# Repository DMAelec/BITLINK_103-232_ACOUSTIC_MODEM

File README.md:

# BITLINK 103-232 ACOUSTIC MODEM

A 74HC943 based acoustic modem running at 300 baud for retro computers.

WORK IN PROGRESS

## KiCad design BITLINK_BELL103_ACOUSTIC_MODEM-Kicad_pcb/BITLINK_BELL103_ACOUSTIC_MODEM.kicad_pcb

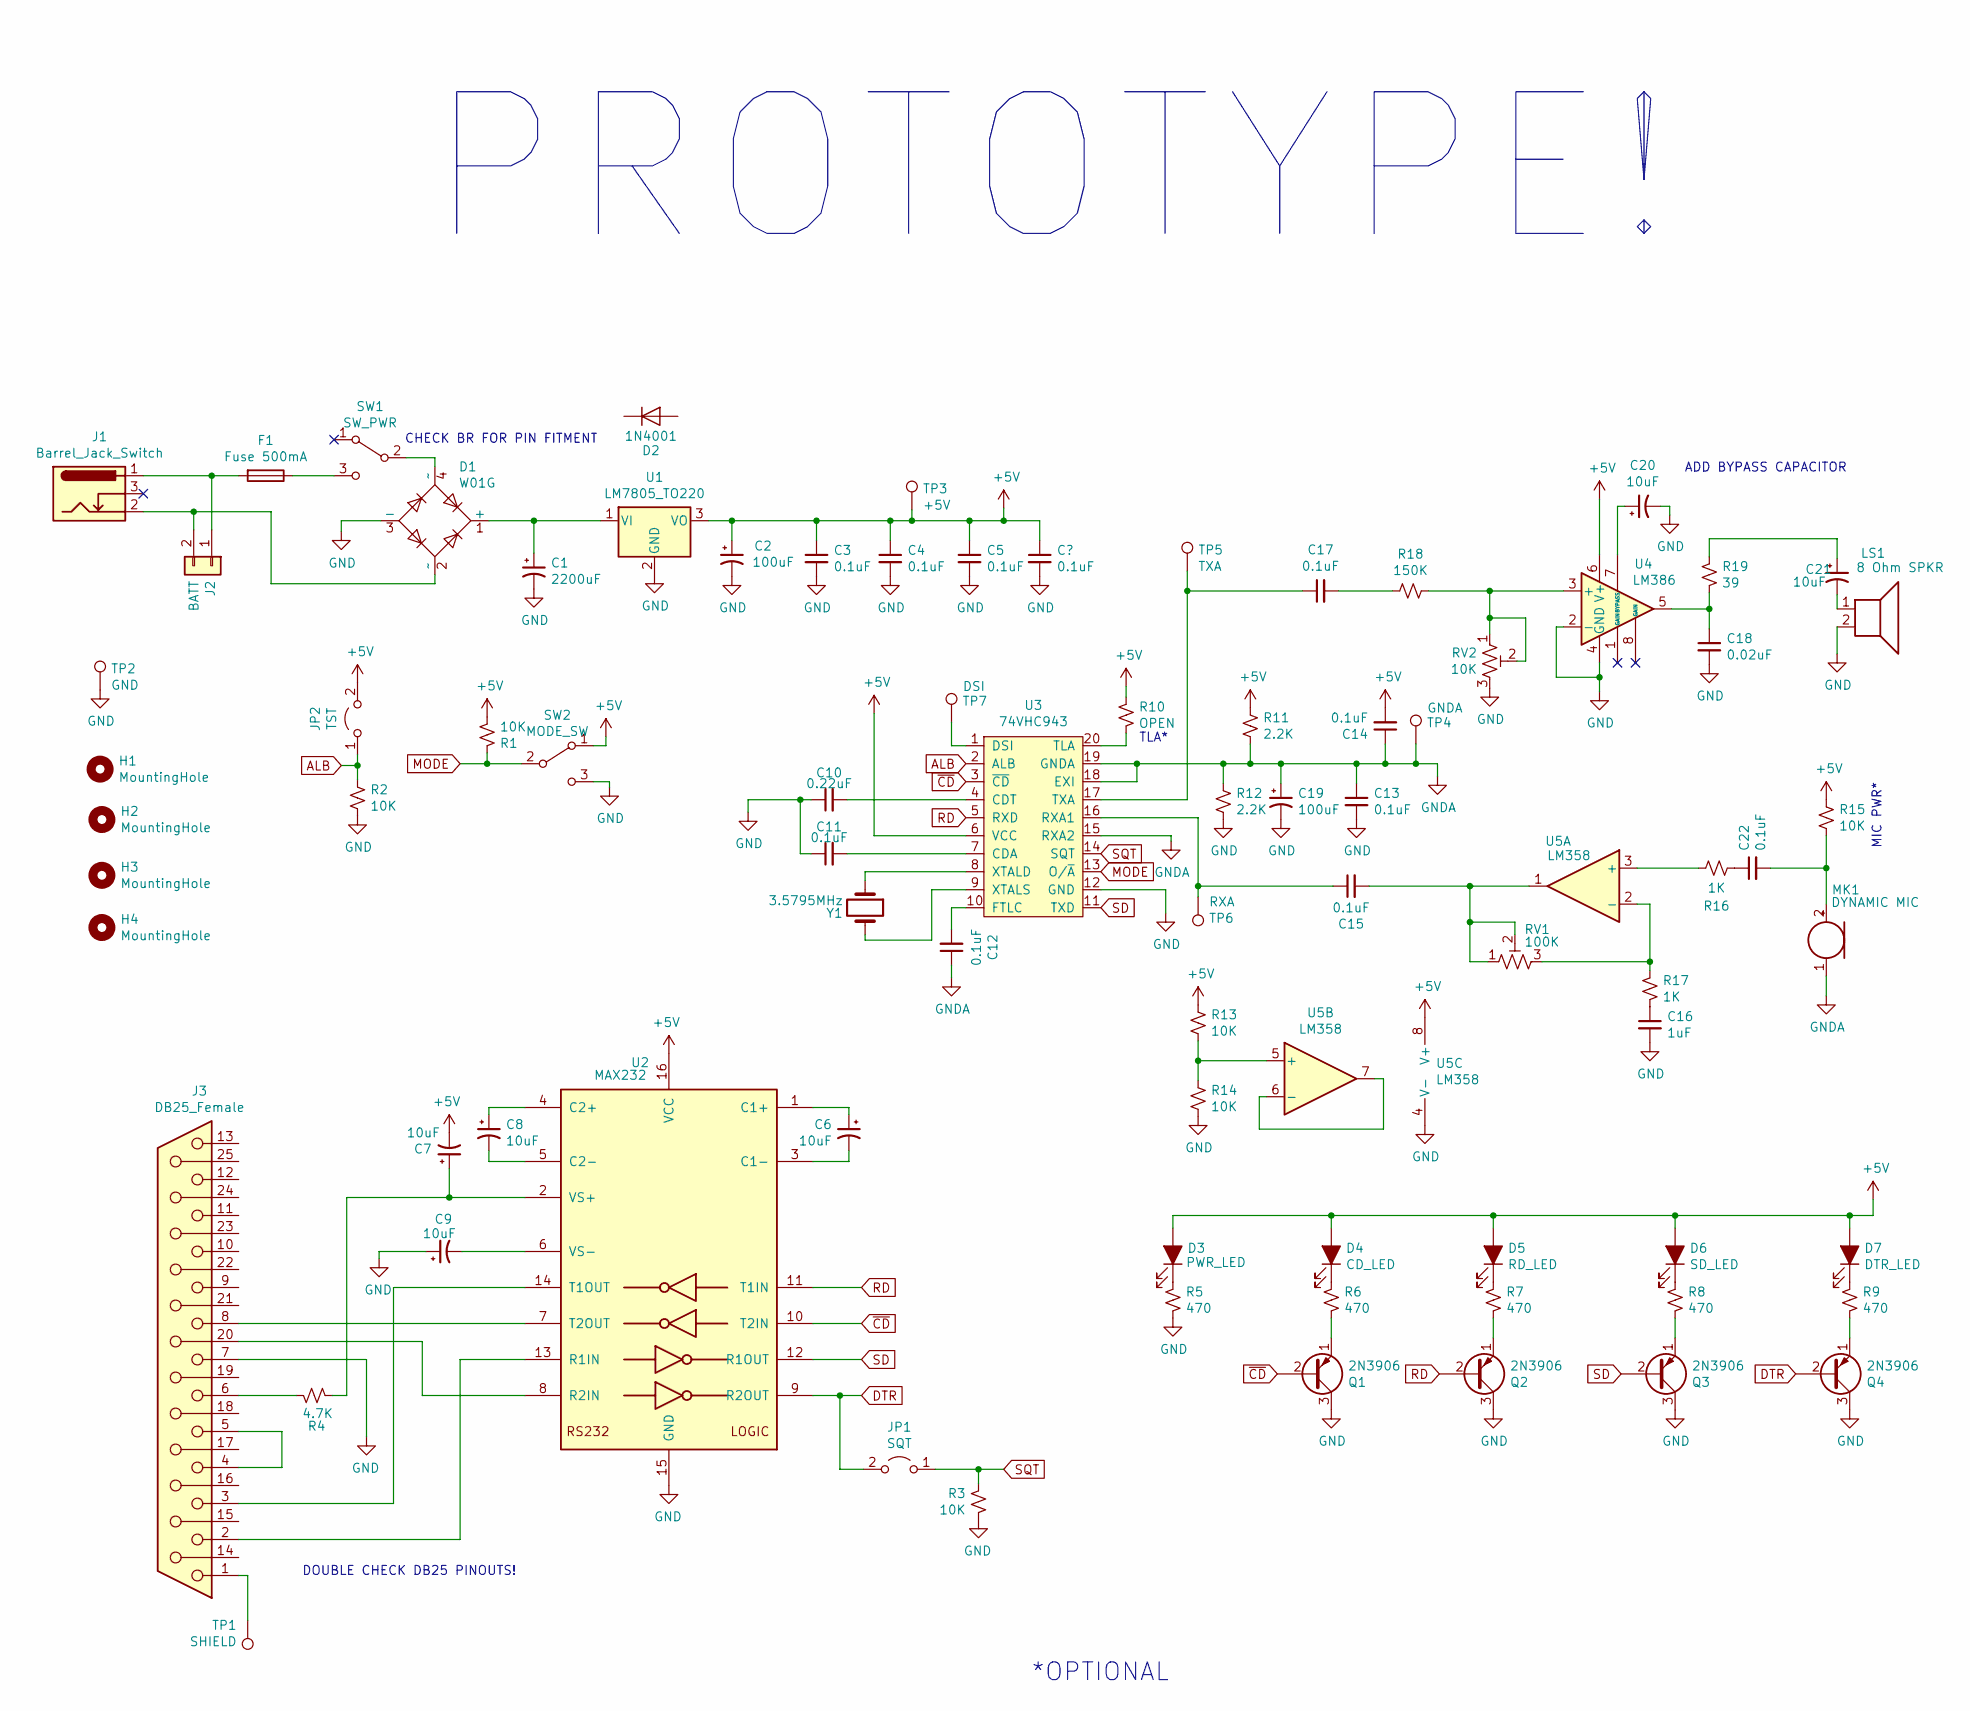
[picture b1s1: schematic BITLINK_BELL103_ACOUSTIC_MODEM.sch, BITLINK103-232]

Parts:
C1: 2200uF; CP_Axial_L30.0mm_D18.0mm_P35.00mm_Horizontal
C2, C19: 100uF; CP_Radial_D8.0mm_P3.80mm
C3, C4, C5, C11, C12, C13, C14, C15, C17, C22: 0.1uF; C_Disc_D5.1mm_W3.2mm_P5.00mm
C6, C7, C8, C9, C20, C21: 10uF; CP_Radial_D5.0mm_P2.50mm
C10: 0.22uF; C_Disc_D5.1mm_W3.2mm_P5.00mm
C16: 1uF; C_Disc_D5.1mm_W3.2mm_P5.00mm
C18: 0.02uF; C_Disc_D5.1mm_W3.2mm_P5.00mm
D1: W01G; Diode_Bridge_Round_D9.8mm
D2: 1N4001; D_DO-41_SOD81_P10.16mm_Horizontal
D3: PWR_LED; LED_D5.0mm
D4: CD_LED; LED_D5.0mm
D5: RD_LED; LED_D5.0mm
D6: SD_LED; LED_D5.0mm
D7: DTR_LED; LED_D5.0mm
F1: Fuse 500mA; Fuseholder_Cylinder-5x20mm_Schurter_0031_8201_Horizontal_Op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
H1, H2, H3, H4: MountingHole; MountingHole_3.2mm_M3
J1: Barrel_Jack_Switch; BarrelJack_Horizontal
J2: BATT; TerminalBlock_bornier-2_P5.08mm
J3: DB25_Female; DSUB-25_Female_Horizontal_P2.77x2.84mm_EdgePinOffset4.94mm_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
JP1: SQT; PinHeader_1x02_P2.54mm_Vertical
JP2: TST; PinHeader_1x02_P2.54mm_Vertical
LS1: 8 Ohm SPKR; Molex_KK-254_AE-6410-02A_1x02_P2.54mm_Vertical
MK1: DYNAMIC MIC; Molex_KK-254_AE-6410-02A_1x02_P2.54mm_Vertical
Q1, Q2, Q3, Q4: 2N3906; TO-92_Wide
R1, R2, R3, R13, R14, R15: 10K; R_Axial_DIN0207_L6.3mm_D2.5mm_P10.16mm_Horizontal
R4: 4.7K; R_Axial_DIN0207_L6.3mm_D2.5mm_P10.16mm_Horizontal
R5, R6, R7, R8, R9: 470; R_Axial_DIN0207_L6.3mm_D2.5mm_P10.16mm_Horizontal
R10: OPEN; R_Axial_DIN0207_L6.3mm_D2.5mm_P10.16mm_Horizontal
R11, R12: 2.2K; R_Axial_DIN0207_L6.3mm_D2.5mm_P10.16mm_Horizontal
R16, R17: 1K; R_Axial_DIN0207_L6.3mm_D2.5mm_P10.16mm_Horizontal
R18: 150K; R_Axial_DIN0207_L6.3mm_D2.5mm_P10.16mm_Horizontal
R19: 39; R_Axial_DIN0207_L6.3mm_D2.5mm_P10.16mm_Horizontal
RV1: 100K; Potentiometer_Piher_PT-10-V10_Vertical
RV2: 10K; Potentiometer_Piher_PT-10-V10_Vertical
SW1: SW_PWR; SW_CK_E101J1ABE2_SPDT_RIGHT_ANGLE_ROCKER
SW2: MODE_SW; SW_CK_E101J1ABE2_SPDT_RIGHT_ANGLE_ROCKER
TP1: SHIELD; TestPoint_THTPad_D2.5mm_Drill1.2mm
TP2: GND; TestPoint_THTPad_D2.5mm_Drill1.2mm
TP3: +5V; TestPoint_THTPad_D2.5mm_Drill1.2mm
TP4: GNDA; TestPoint_THTPad_D2.5mm_Drill1.2mm
TP5: TXA; TestPoint_THTPad_D2.5mm_Drill1.2mm
TP6: RXA; TestPoint_THTPad_D2.5mm_Drill1.2mm
TP7: DSI; TestPoint_THTPad_D2.5mm_Drill1.2mm
U1: LM7805_TO220; TO-220-3_Horizontal_TabDown
U2: MAX232; DIP-16_W7.62mm_LongPads
U3: 74VHC943; DIP-20_W7.62mm_LongPads
U4: LM386; DIP-8_W7.62mm_LongPads
U5: LM358; DIP-8_W7.62mm_LongPads
Y1: 3.5795MHz; Crystal_HC49-U_Vertical

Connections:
+5V: C2.1, C3.1, C4.1, C5.1, C7.2, C14.2, D3.2 (A), D4.2 (A), D5.2 (A), D6.2 (A), D7.2 (A), JP2.2 (B), R1.2, R10.1, R11.1, R13.1, R15.1, SW2.1 (A), TP3.1, U1.3 (VO), U2.16 (VCC), U3.6 (VCC), U4.6 (V+), U5.8 (V+)
ALB: JP2.1 (A), R2.1, U3.2 (ALB)
DTR: JP1.2 (B), Q4.2 (B), U2.9 (R2OUT)
GND: C1.2, C2.2, C3.2, C4.2, C5.2, C9.1, C10.1, C11.1, C13.2, C16.2, C18.2, C19.2, C20.2, D1.3 (-), J3.7, LS1.2, Q1.3 (C), Q2.3 (C), Q3.3 (C), Q4.3 (C), R2.2, R3.2, R5.2, R12.2, R14.2, RV2.3, SW2.3 (C), TP2.1, U1.2 (GND), U2.15 (GND), U3.12 (GND), U4.2 (-), U4.4 (GND), U5.4 (V-)
GNDA: C12.1, C13.1, C14.1, C19.1, MK1.1 (-), R11.2, R12.1, TP4.1, U3.15 (RXA2), U3.18 (EXI), U3.19 (GNDA)
MODE: R1.1, SW2.2 (B), U3.13 (O/~A)
unnamed: C1.1, D1.1 (+), U1.1 (VI)
unnamed: C6.1, U2.1 (C1+)
unnamed: C6.2, U2.3 (C1-)
unnamed: C7.1, R4.1, U2.2 (VS+)
unnamed: C8.1, U2.4 (C2+)
unnamed: C8.2, U2.5 (C2-)
unnamed: C9.2, U2.6 (VS-)
unnamed: C10.2, U3.4 (CDT)
unnamed: C11.2, U3.7 (CDA)
unnamed: C12.2, U3.10 (FTLC)
unnamed: C15.1, TP6.1, U3.16 (RXA1)
unnamed: C15.2, RV1.1, RV1.2, U5.1
unnamed: C16.1, R17.2
unnamed: C17.1, TP5.1, U3.17 (TXA)
unnamed: C17.2, R18.2
unnamed: C18.1, R19.2, U4.5
unnamed: C20.1, U4.7 (BYPASS)
unnamed: C21.1, R19.1
unnamed: C21.2, LS1.1
unnamed: C22.1, R16.1
unnamed: C22.2, MK1.2 (+), R15.2
unnamed: D1.2 (~~), J1.2, J2.2
unnamed: D1.4 (~~), SW1.2 (B)
unnamed: D3.1 (K), R5.1
unnamed: D4.1 (K), R6.1
unnamed: D5.1 (K), R7.1
unnamed: D6.1 (K), R8.1
unnamed: D7.1 (K), R9.1
unnamed: F1.1, SW1.3 (C)
unnamed: F1.2, J1.1, J2.1
unnamed: J3.1, TP1.1
unnamed: J3.2, U2.13 (R1IN)
unnamed: J3.3, U2.14 (T1OUT)
unnamed: J3.4, J3.5
unnamed: J3.6, R4.2
unnamed: J3.8, U2.7 (T2OUT)
unnamed: J3.20, U2.8 (R2IN)
unnamed: Q1.1 (E), R6.2
unnamed: Q2.1 (E), R7.2
unnamed: Q3.1 (E), R8.2
unnamed: Q4.1 (E), R9.2
unnamed: R10.2, U3.20 (TLA)
unnamed: R13.2, R14.1, U5.5 (+)
unnamed: R16.2, U5.3 (+)
unnamed: R17.1, RV1.3, U5.2 (-)
unnamed: R18.1, RV2.1, RV2.2, U4.3 (+)
unnamed: TP7.1, U3.1 (DSI)
unnamed: U3.8 (XTALD), Y1.1
unnamed: U3.9 (XTALS), Y1.2
unnamed: U5.6 (-), U5.7
RD: Q2.2 (B), U2.11 (T1IN), U3.5 (RXD)
SD: Q3.2 (B), U2.12 (R1OUT), U3.11 (TXD)
SQT: JP1.1 (A), R3.1, U3.14 (SQT)
~CD: Q1.2 (B), U2.10 (T2IN), U3.3 (~CD)

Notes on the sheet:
MIC PWR*
PROTOTYPE!
*OPTIONAL
TLA*
DOUBLE CHECK DB25 PINOUTS!
ADD BYPASS CAPACITOR
CHECK BR FOR PIN FITMENT

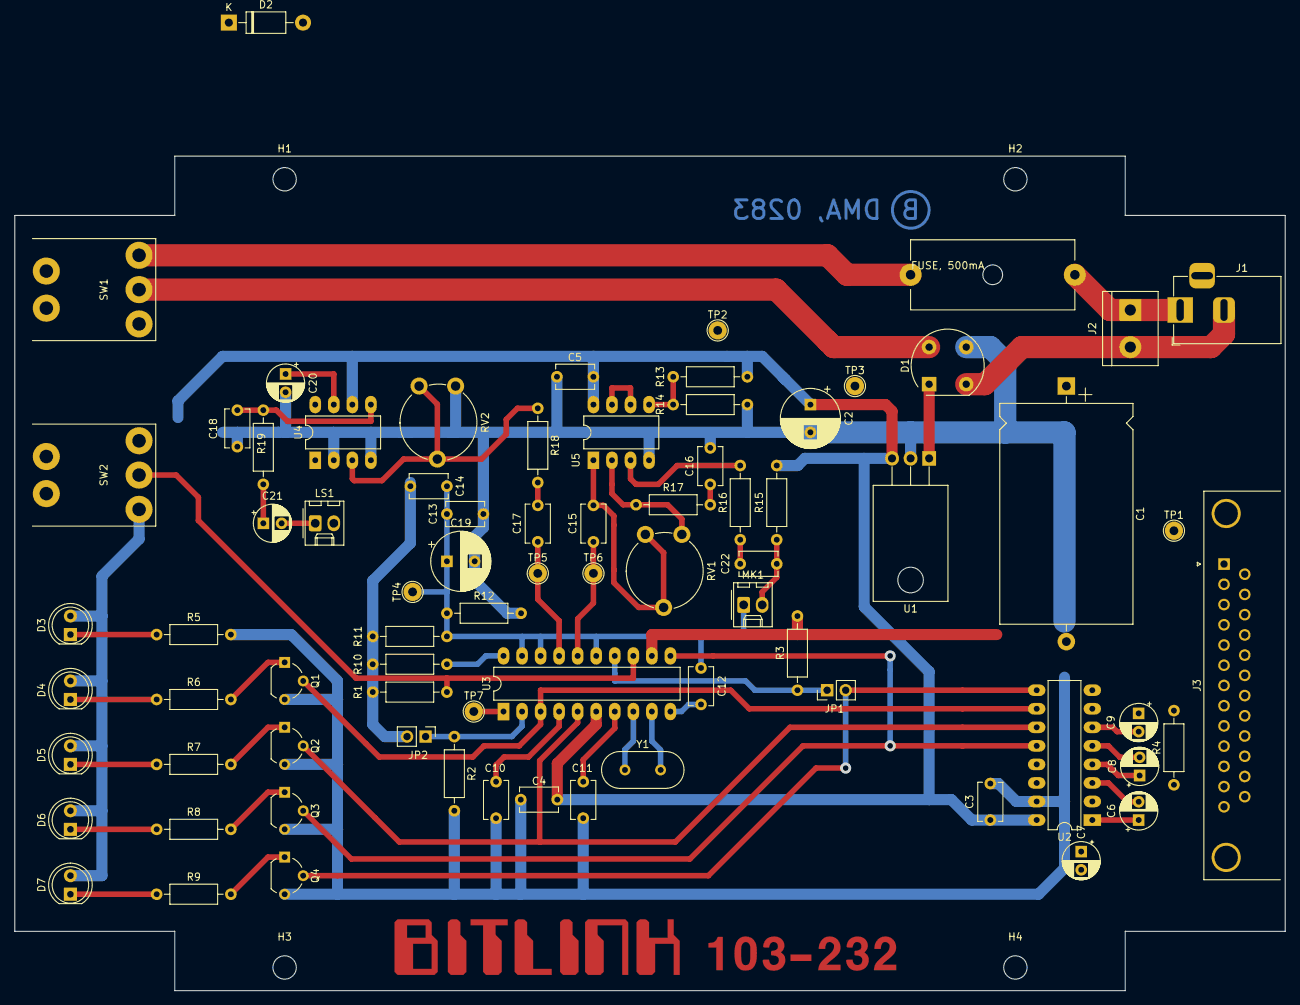
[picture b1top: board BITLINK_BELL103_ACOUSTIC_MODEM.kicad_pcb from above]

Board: 2 copper layers, 174.0 x 114.3 mm, 81 parts (0 on the bottom side), 60 nets.
